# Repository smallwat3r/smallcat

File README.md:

# Smallcat

A diodeless 26-key keyboard, featuring the purr-fect code reviewer, my cat, Lila.

This repo contains Gerber files, KiCad files, my keymap, and links to QMK and Vial-QMK firmware for the Smallcat.

## Versions

There are two versions of the Smallcat: **split** and **unibody**.

Both versions share the same column splay:

| Finger | Splay |
|--------|-------|
| Pinkie | 10°   |
| Ring   | 5°    |
| Middle | 2°    |

### Split

| Component | Specification |
|-----------|---------------|
| Controller | 2x RP2040-Zero footprint ([example](https://www.waveshare.com/wiki/RP2040-Zero)) |
| Switches | 26 low profile Choc (soldered) |
| Diodes | None required |
| Connection | TRRS jack |

### Unibody

| Component | Specification |
|-----------|---------------|
| Controller | 1x RP2040 Pro Micro with 28 I/O pins ([example](https://www.aliexpress.com/i/1005006097129434.html)) |
| Switches | 26 low profile Choc (soldered) |
| Diodes | None required |

#### Build notes

The unibody version has a few unconventional details:

- **Pro Micro model**: Use a Pro Micro with extra pins (18 and 24) near the middle of the board.

- **Pin clearance**: The space between pins 18 and 24 is narrow. You may need to trim the plastic between them, just ensure enough remains so the metal contacts don't touch. [See photo](./assets/pins_uni.jpeg). This is a simple workaround to use the extra pins and keep the board diodeless.

- **Pin headers**: PCB holes are narrower than standard. Use machined conical pin headers like [these](https://www.proto-advantage.com/store/datasheets/MPH100IMP40M-G-V-TH.pdf).

- **Controller orientation**: Install component-side up (not face-down like most keyboards). This way the boot and reset buttons are accessible.

## Case

Simple press-fit cases with no screws or hardware. The base is 1mm larger than the PCB, allowing it to slide in snugly. You may need to trim some edges slightly to ensure a tight fit. Small bumpons under the PCB prevent the pins from resting directly on the case.

| Split | Uni |
|-------|-----|
|  |  |

## Firmware

I maintain my own [QMK keymap](https://github.com/smallwat3r/qmk-keymap), which includes my keymap, configuration for the Smallcat, and a ready-to-flash UF2 file.

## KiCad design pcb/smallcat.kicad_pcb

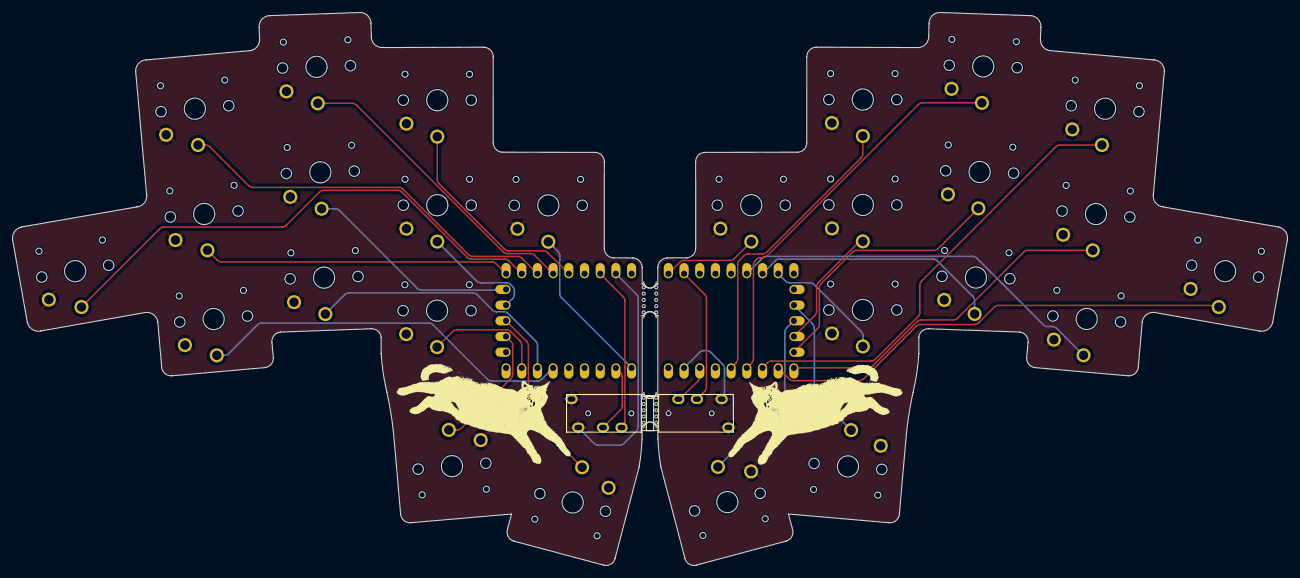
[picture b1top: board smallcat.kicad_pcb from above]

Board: 2 copper layers, 206.4 x 89.5 mm, 32 parts (0 on the bottom side), 30 nets.

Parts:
J1, J2: AudioJack4dpb; TRRS-PJ-320A
SW3, SW3_r1, SW4, SW4_r1, SW5, SW5_r1, SW7_r1, SW8, SW8_r1, SW9, SW9_r1, SW10, SW11, SW11_r1, SW11_r1#2, SW12, SW12_r1, SW15, SW15_r1, SW16, SW17, SW18_r1, SW20, SW20_r1, SW21, SW21_r1: SW_Push; choc-v1-with-millmax
U?: rp2040-zero-tht
U?#2: rp2040-zero-tht
mouse-bite-2mm-slot, mouse-bite-2mm-slot#2: VAL**; mouse-bite-5mm-slot-with-space-for-track

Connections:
Switch2: SW3.1, U?#2.17
Switch2_r: SW3_r1.1, U?.17
Switch3: SW4.1, U?#2.18
Switch3_r: SW4_r1.1, U?.18
Switch4: SW5.1, U?#2.19
Switch4_r: SW5_r1.1, U?.19
Switch6: SW8.1, U?#2.16
Switch6_r: SW7_r1.1, U?.16
Switch7: SW9.1, U?#2.15
Switch7_r: SW8_r1.1, U?.15
Switch8: SW10.1, U?#2.14
Switch8_r: SW9_r1.1, U?.14
Switch9: SW11.1, U?#2.13
Switch9_r: SW11_r1.1, U?.13
Switch10: SW12.1, U?#2.1
Switch10_r: SW12_r1.1, U?.1
Switch12: SW15.1, U?#2.6
Switch12_r: SW18_r1.1, U?.6
Switch13: SW16.1, U?#2.7
Switch13_r: SW15_r1.1, U?.7
Switch14: SW17.1, U?#2.8
Switch14_r: SW11_r1#2.1, U?.8
Switch16: SW21.1, U?#2.11
Switch16_r: SW21_r1.1, U?.11
Switch17: SW20.1, U?#2.12
Switch17_r: SW20_r1.1, U?.12
Switch18: J2.R1, U?#2.2
Switch18_r: J1.R1, U?.2
gnd: J1.S, J1.T, J2.S, J2.T, SW3.2, SW3_r1.2, SW4.2, SW4_r1.2, SW5.2, SW5_r1.2, SW7_r1.2, SW8.2, SW8_r1.2, SW9.2, SW9_r1.2, SW10.2, SW11.2, SW11_r1.2, SW11_r1#2.2, SW12.2, SW12_r1.2, SW15.2, SW15_r1.2, SW16.2, SW17.2, SW18_r1.2, SW20.2, SW20_r1.2, SW21.2, SW21_r1.2, U?.22, U?#2.22
vcc: J1.R2, J2.R2, U?.21, U?#2.21

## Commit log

2024-10-26 Add files
2024-10-26 Edit README
2024-10-26 Add versioning
2024-11-02 Update firmware
2024-11-04 Add case designs
2024-11-04 Fix typo
2024-11-10 Add fusion case file
2025-01-02 Add source firmware files
2025-01-26 Add more recent firmware
2025-01-26 Add README to firmware
2025-01-29 Add firmware files into default repo
2025-02-14 Add QMK config links
2025-02-14 Replace firmware
2025-02-15 Add links to firmware sources
2025-03-16 Replace images not rendering properly
2025-03-16 Edit image
2025-03-16 Add image of PCB
2025-07-26 Add unibody board
2025-07-26 Fix file
2025-08-04 Add production file for uni
2026-01-16 Add openscad cases
2026-01-16 Better structure
2026-01-16 Move gerber to pcb directly
2026-01-16 Remove deprecated note
2026-01-16 Snuggier fit
2026-01-16 Add photo at bottom
2026-01-16 Move images to assets
2026-01-16 Add case pictures
2026-01-16 Better image compression
2026-01-16 OpenSCAD cases (#4)
    * Add openscad cases
    * Better structure
    * Move gerber to pcb directly
    * Remove deprecated note
    * Snuggier fit
    * Updates
2026-02-10 Remove v1.0 prefixes
